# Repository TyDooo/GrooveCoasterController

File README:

# Groove Coaster controller (WIP)
Welcome to the Groove Coaster Arcade Controller project! This project aims to create a custom Groove Coaster arcade controller using real arcade parts, a Raspberry Pi Pico, and custom PCBs with Neopixels for enhanced lighting control. With this controller, you can enjoy the Groove Coaster experience at home!

**This project is very much work in progress and is not ready for use yet!**

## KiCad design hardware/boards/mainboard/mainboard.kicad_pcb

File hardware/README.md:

# Hardware

## Mainboard

### TODO
- [ ] Verify if correct JST connectors
- [ ] Verify if booster pin connections are correct
- [ ] Add connectors for extra buttons
- [ ] Determine Neopixel data lines

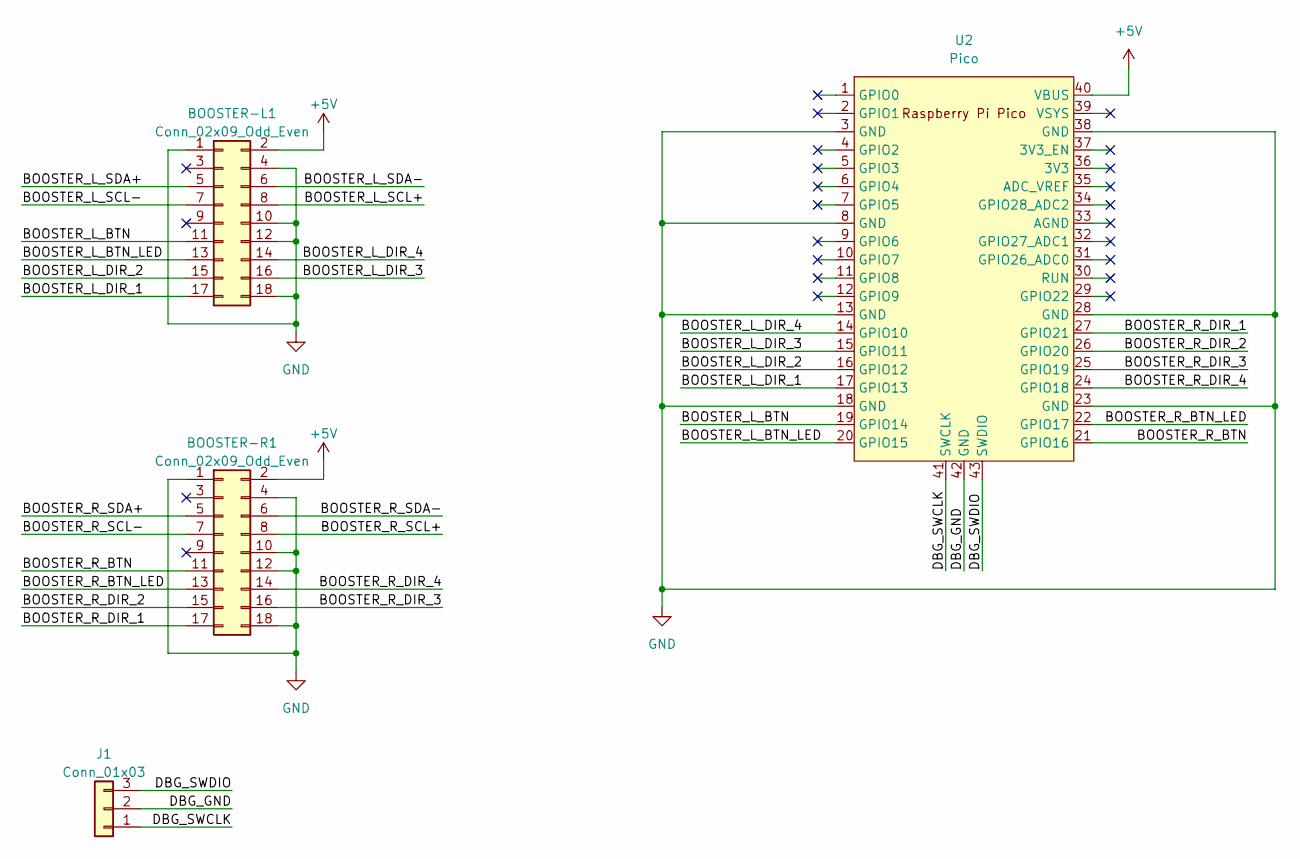
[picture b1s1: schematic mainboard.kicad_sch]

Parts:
BOOSTER-L1: Conn_02x09_Odd_Even; JST_PUD_B18B-PUDSS_2x09_P2.00mm_Vertical
BOOSTER-R1: Conn_02x09_Odd_Even; JST_PUD_B18B-PUDSS_2x09_P2.00mm_Vertical
J1: Conn_01x03; JST_PH_B3B-PH-K_1x03_P2.00mm_Vertical
U2: Pico; RPi_Pico_SMD_TH_Clean

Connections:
+5V: BOOSTER-L1.2, BOOSTER-R1.2, U2.40 (VBUS)
/BOOSTER_L_BTN: BOOSTER-L1.11, U2.19 (GPIO14)
/BOOSTER_L_BTN_LED: BOOSTER-L1.13, U2.20 (GPIO15)
/BOOSTER_L_DIR_1: BOOSTER-L1.17, U2.17 (GPIO13)
/BOOSTER_L_DIR_2: BOOSTER-L1.15, U2.16 (GPIO12)
/BOOSTER_L_DIR_3: BOOSTER-L1.16, U2.15 (GPIO11)
/BOOSTER_L_DIR_4: BOOSTER-L1.14, U2.14 (GPIO10)
/BOOSTER_L_SCL+: BOOSTER-L1.8
/BOOSTER_L_SCL-: BOOSTER-L1.7
/BOOSTER_L_SDA+: BOOSTER-L1.5
/BOOSTER_L_SDA-: BOOSTER-L1.6
/BOOSTER_R_BTN: BOOSTER-R1.11, U2.21 (GPIO16)
/BOOSTER_R_BTN_LED: BOOSTER-R1.13, U2.22 (GPIO17)
/BOOSTER_R_DIR_1: BOOSTER-R1.17, U2.27 (GPIO21)
/BOOSTER_R_DIR_2: BOOSTER-R1.15, U2.26 (GPIO20)
/BOOSTER_R_DIR_3: BOOSTER-R1.16, U2.25 (GPIO19)
/BOOSTER_R_DIR_4: BOOSTER-R1.14, U2.24 (GPIO18)
/DBG_GND: J1.2, U2.42 (GND)
/DBG_SWCLK: J1.1, U2.41 (SWCLK)
/DBG_SWDIO: J1.3, U2.43 (SWDIO)
BOOSTER_R_SCL+: BOOSTER-R1.8
BOOSTER_R_SCL-: BOOSTER-R1.7
BOOSTER_R_SDA+: BOOSTER-R1.5
BOOSTER_R_SDA-: BOOSTER-R1.6
GND: BOOSTER-L1.1, BOOSTER-L1.4, BOOSTER-L1.10, BOOSTER-L1.12, BOOSTER-L1.18, BOOSTER-R1.1, BOOSTER-R1.4, BOOSTER-R1.10, BOOSTER-R1.12, BOOSTER-R1.18, U2.3 (GND), U2.8 (GND), U2.13 (GND), U2.18 (GND), U2.23 (GND), U2.28 (GND), U2.38 (GND)

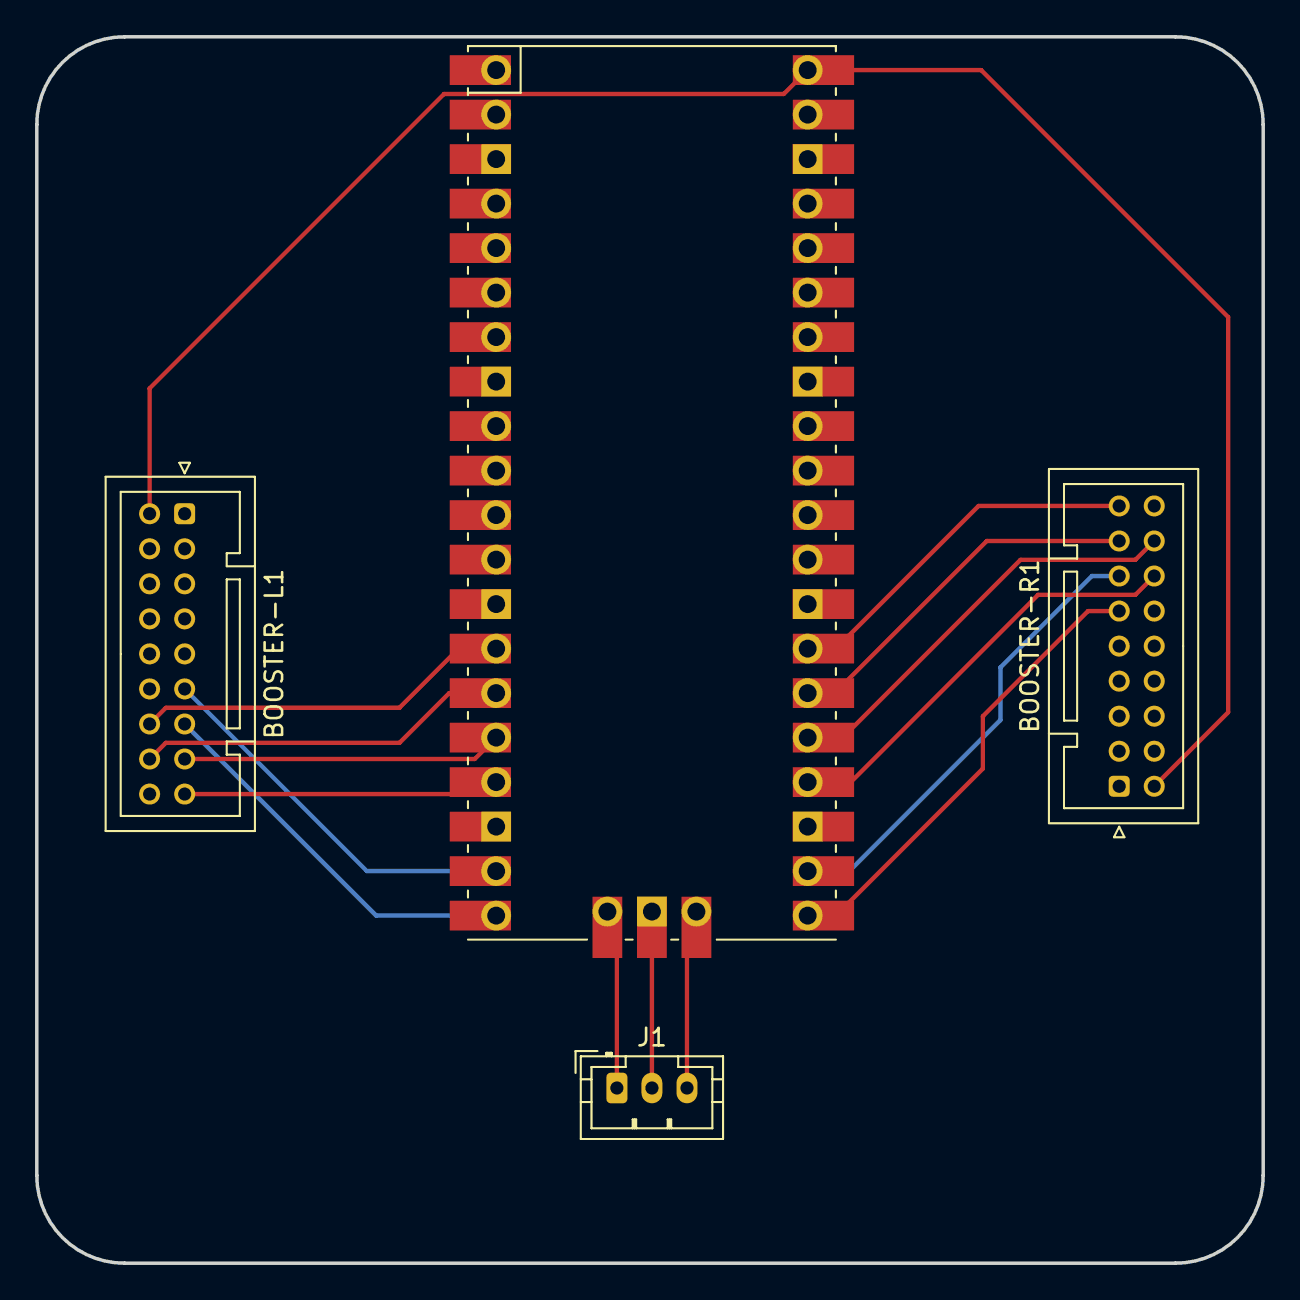
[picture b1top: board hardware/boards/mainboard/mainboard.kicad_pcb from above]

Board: 2 copper layers, 70.0 x 70.0 mm, 4 parts (0 on the bottom side), 17 nets.

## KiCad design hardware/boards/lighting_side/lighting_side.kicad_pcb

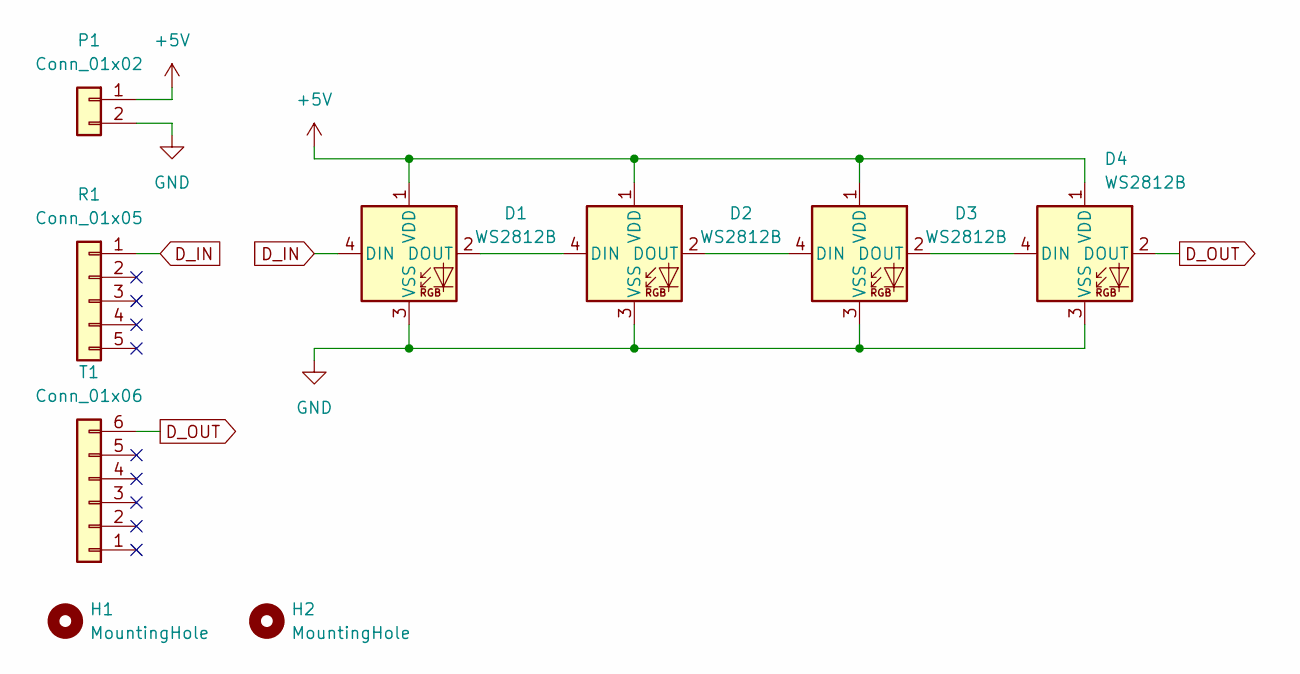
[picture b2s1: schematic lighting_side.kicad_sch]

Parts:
D1, D2, D3, D4: WS2812B; LED_WS2812B_PLCC4_5.0x5.0mm_P3.2mm
H1, H2: MountingHole; MountingHole_5mm
P1: Conn_01x02; JST_XH_S2B-XH-A_1x02_P2.50mm_Horizontal
R1: Conn_01x05; JST_PH_S5B-PH-K_1x05_P2.00mm_Horizontal
T1: Conn_01x06; JST_PH_S6B-PH-K_1x06_P2.00mm_Horizontal

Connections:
+5V: D1.1 (VDD), D2.1 (VDD), D3.1 (VDD), D4.1 (VDD), P1.1
D_IN: D1.4 (DIN), R1.1
D_OUT: D4.2 (DOUT), T1.6
GND: D1.3 (VSS), D2.3 (VSS), D3.3 (VSS), D4.3 (VSS), P1.2
unnamed: D1.2 (DOUT), D2.4 (DIN)
unnamed: D2.2 (DOUT), D3.4 (DIN)
unnamed: D3.2 (DOUT), D4.4 (DIN)

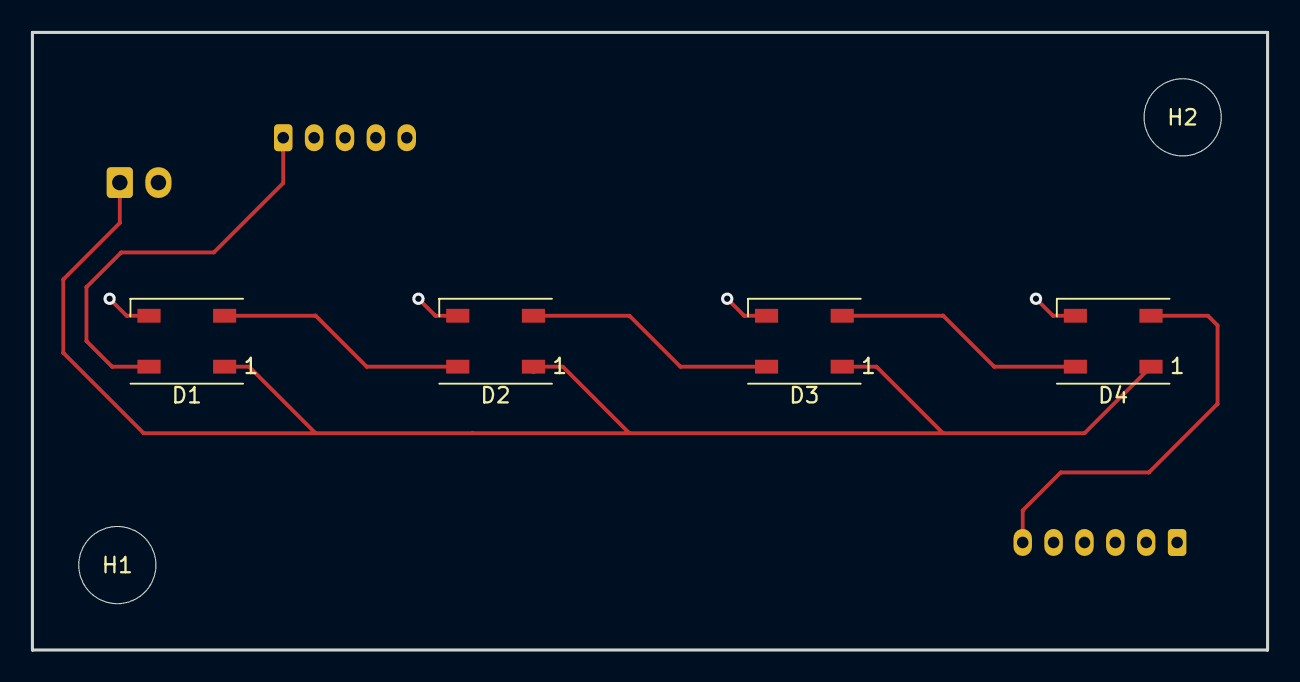
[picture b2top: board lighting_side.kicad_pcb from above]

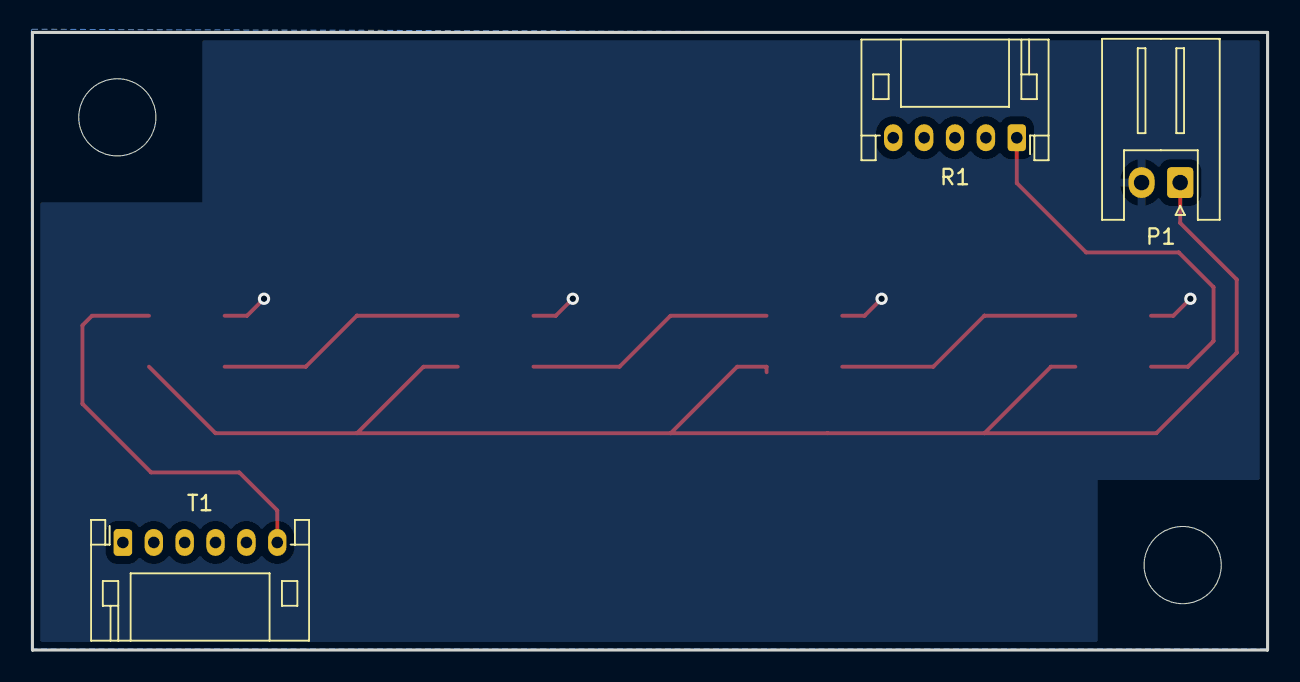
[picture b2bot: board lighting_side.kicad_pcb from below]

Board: 2 copper layers, 80.0 x 40.0 mm, 9 parts (3 on the bottom side), 7 nets.

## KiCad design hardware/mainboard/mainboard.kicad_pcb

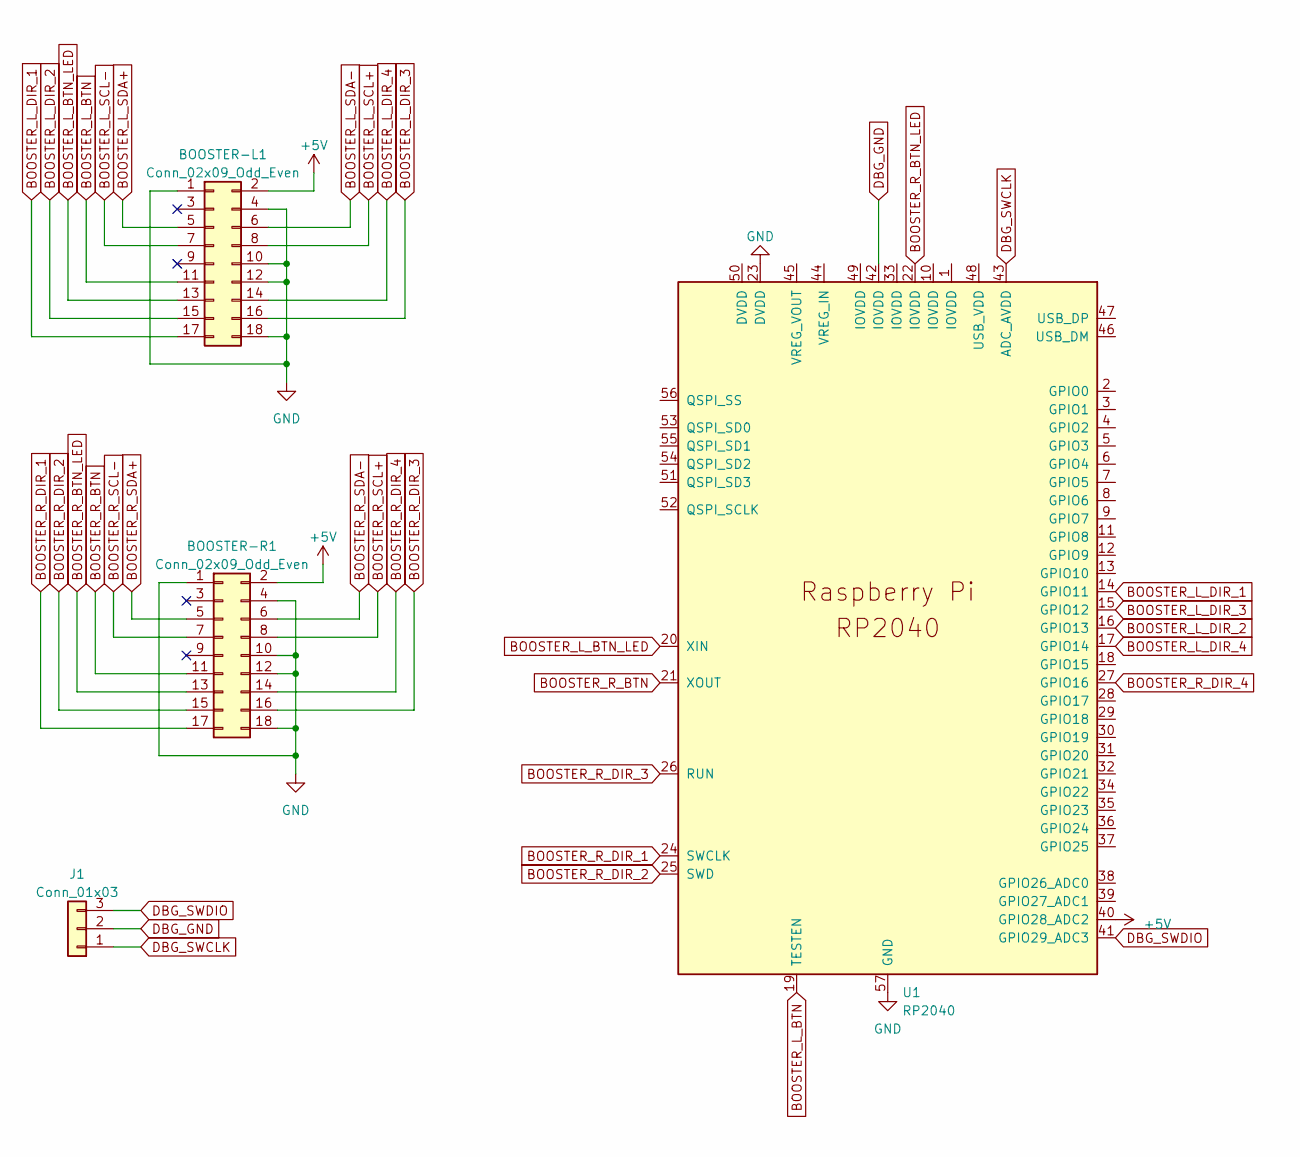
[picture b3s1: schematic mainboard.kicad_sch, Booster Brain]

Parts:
BOOSTER-L1: Conn_02x09_Odd_Even; JST_PUD_B18B-PUDSS_2x09_P2.00mm_Vertical
BOOSTER-R1: Conn_02x09_Odd_Even; JST_PUD_B18B-PUDSS_2x09_P2.00mm_Vertical
J1: Conn_01x03; JST_PH_B3B-PH-K_1x03_P2.00mm_Vertical
U1: RP2040; RPi_Pico_SMD_TH

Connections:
+5V: BOOSTER-L1.2, BOOSTER-R1.2, U1.40 (GPIO28_ADC2)
BOOSTER_L_BTN: BOOSTER-L1.11, U1.19 (TESTEN)
BOOSTER_L_BTN_LED: BOOSTER-L1.13, U1.20 (XIN)
BOOSTER_L_DIR_1: BOOSTER-L1.17, U1.14 (GPIO11)
BOOSTER_L_DIR_2: BOOSTER-L1.15, U1.16 (GPIO13)
BOOSTER_L_DIR_3: BOOSTER-L1.16, U1.15 (GPIO12)
BOOSTER_L_DIR_4: BOOSTER-L1.14, U1.17 (GPIO14)
BOOSTER_L_SCL+: BOOSTER-L1.8
BOOSTER_L_SCL-: BOOSTER-L1.7
BOOSTER_L_SDA+: BOOSTER-L1.5
BOOSTER_L_SDA-: BOOSTER-L1.6
BOOSTER_R_BTN: BOOSTER-R1.11, U1.21 (XOUT)
BOOSTER_R_BTN_LED: BOOSTER-R1.13, U1.22 (IOVDD)
BOOSTER_R_DIR_1: BOOSTER-R1.17, U1.24 (SWCLK)
BOOSTER_R_DIR_2: BOOSTER-R1.15, U1.25 (SWD)
BOOSTER_R_DIR_3: BOOSTER-R1.16, U1.26 (RUN)
BOOSTER_R_DIR_4: BOOSTER-R1.14, U1.27 (GPIO16)
BOOSTER_R_SCL+: BOOSTER-R1.8
BOOSTER_R_SCL-: BOOSTER-R1.7
BOOSTER_R_SDA+: BOOSTER-R1.5
BOOSTER_R_SDA-: BOOSTER-R1.6
DBG_GND: J1.2, U1.42 (IOVDD)
DBG_SWCLK: J1.1, U1.43 (ADC_AVDD)
DBG_SWDIO: J1.3, U1.41 (GPIO29_ADC3)
GND: BOOSTER-L1.1, BOOSTER-L1.4, BOOSTER-L1.10, BOOSTER-L1.12, BOOSTER-L1.18, BOOSTER-R1.1, BOOSTER-R1.4, BOOSTER-R1.10, BOOSTER-R1.12, BOOSTER-R1.18, U1.23 (DVDD), U1.57 (GND)

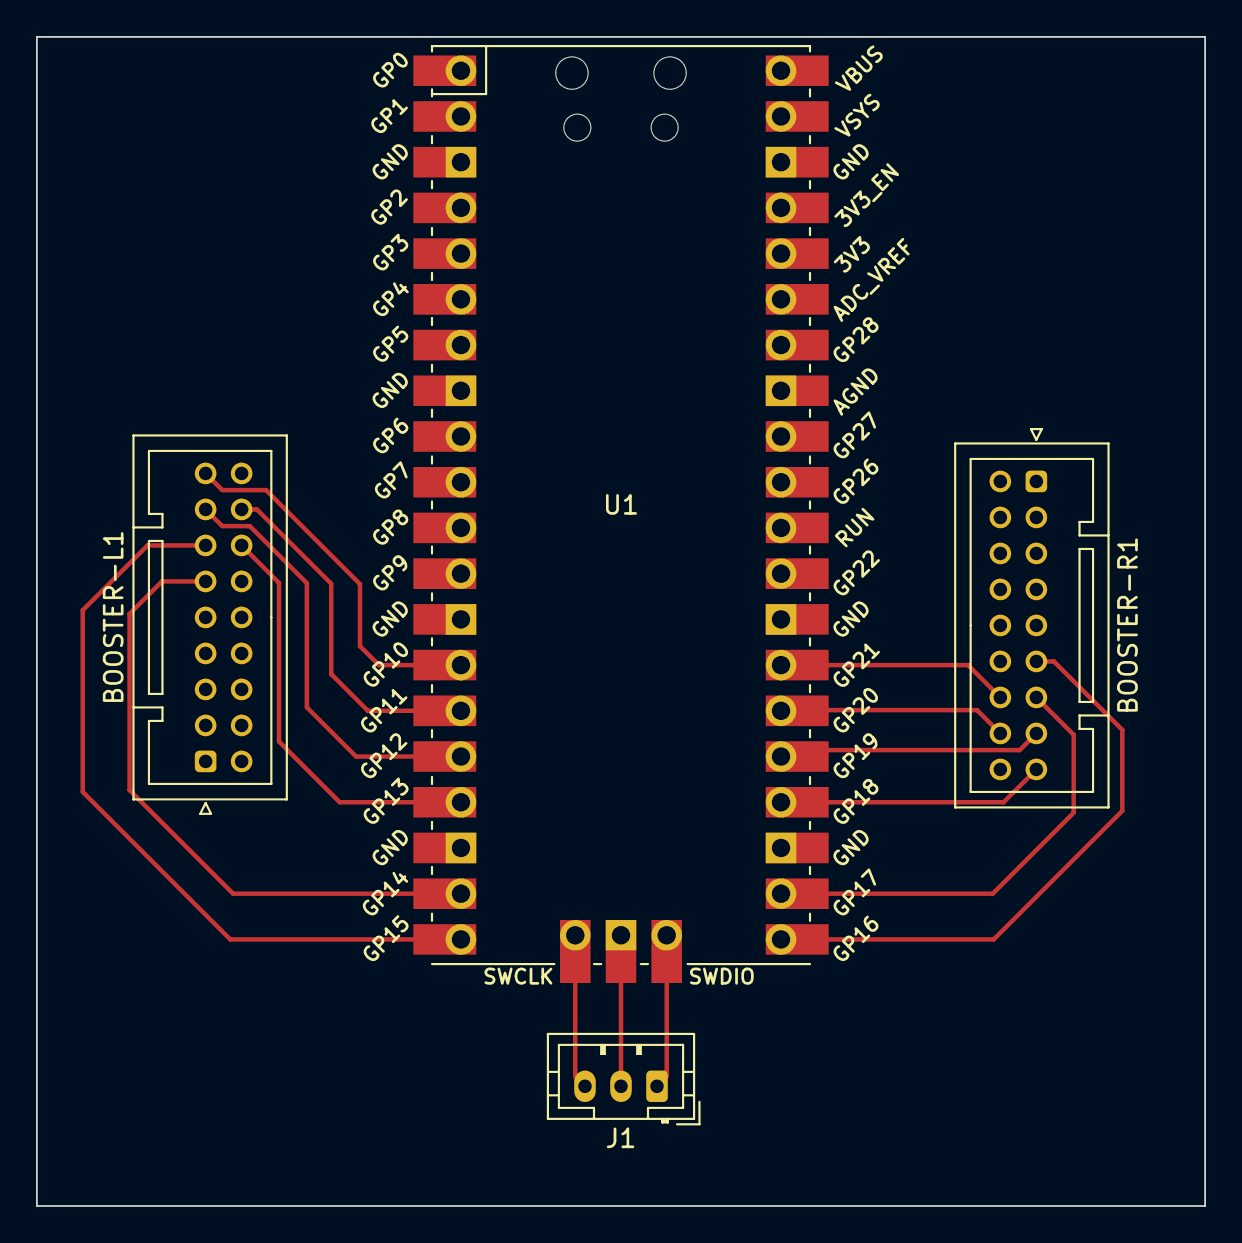
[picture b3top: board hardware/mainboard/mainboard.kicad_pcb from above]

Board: 2 copper layers, 64.9 x 65.0 mm, 4 parts (0 on the bottom side), 17 nets.

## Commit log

2022-11-11 Use debouncer
2022-11-13 change R to ABXY
2022-11-18 Remove pro micro related code
2022-12-05 setup MPG joystick lib and earlephilhower core
2023-04-12 build(firmware): :tada: Setup cmake project with pico-sdk
2023-04-16 feat(firmware): :sparkles: Send gampad HID report over USB and map dpad, buttons
2023-04-16 chore: :heavy_plus_sign: Add pico-sdk as submodule
2023-04-16 chore(hardware): :bento: Add KiCad projects in their current state
2023-04-16 chore: :truck: Rename README to README.md
2023-04-16 docs: :memo: Extend the README with various sections
2023-04-16 refactor(firmware): :truck: Move firmware related files and folders to the firmware folder
2023-04-16 chore: :page_facing_up: Add license
2023-04-17 feat(firmware): :sparkles: Add debouncing for buttons and dpad
2023-04-17 build(firmware): :hammer: Enable extra compiler options
2023-04-22 chore(hardware): :truck: Move KiCad projects to boards folder
2023-04-22 chore(hardware): :heavy_plus_sign: Add Raspberry PI Pico KiCad symbols and footprints
2023-05-01 refactor(firmware): :sparkles: Track state per booster
    The state is now kept and tracked per booster. This is done in preparation of the upcoming lighting changes.
2023-05-07 chore(firmware): :arrow_up: Bump pico-sdk to latest develop
    Bump the pico-sdk to the latest develop to fix an issue after upgrading to GCC 13
2023-05-07 Add the ability to communicate with ws2812 LEDs
2023-07-08 refactor(hardware): refactor mainboard
2023-07-08 chore: Add conventional commit scopes to vscode settings
2023-07-08 chore(firmware): :arrow_up: bump pico-sdk to latest master
2023-11-02 chore(firmware): add a nix flake and move pico-sdk to flake
2023-11-03 chore: move firmware contents to repo root
2023-11-05 chore: add .envrc file
2023-11-07 refactor: use MPG lib and c++
2024-05-30 chore: Add .envrc file with flake configuration
2024-05-31 chore: Update flake configuration and dependencies
2025-06-16 chore: bump pico-sdk and update nix flake configuration
2025-06-16 refactor: move header files to src
2025-12-20 Add initial implementation of Booster class
2025-12-23 Add FastLED
2025-12-27 Per segment lighting
2025-12-27 Add diagonal smoothing
2025-12-30 Add breathing effect
2025-12-30 Clean up joystick to gamepad direction mapping
2025-12-30 Update formatting
2025-12-30 Add license and extend readme
    The readme now includes a small section about the lighting system
2026-01-04 Add right booster LEDs
2026-01-12 Bring up-to-date with HW changes and improve latency
2026-01-12 Add picture of the current state
2026-01-13 Add ripple effect for booster movement
2026-01-14 Effect and Effect manager class and new animation
2026-01-14 Add HoldSolidEffect effect for dual hold
2026-01-14 Add dual press animation
2026-01-14 Fix memory leak... whoops
2026-01-15 Refactor
2026-01-15 Run lighting on core1
